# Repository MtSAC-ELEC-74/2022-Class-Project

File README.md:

# MtSAC ELEC 74 Spring Class Project
Please be aware that any contributions you make to this project are avaible to the public.

## KiCAD
Please use KiCAD V5.1.12 with this project.

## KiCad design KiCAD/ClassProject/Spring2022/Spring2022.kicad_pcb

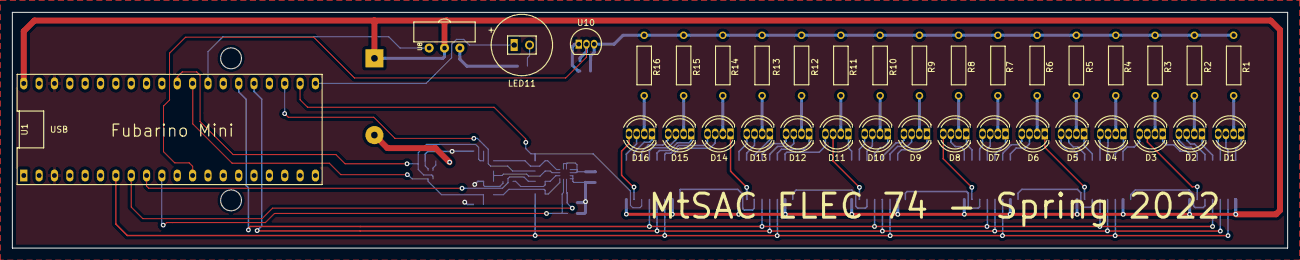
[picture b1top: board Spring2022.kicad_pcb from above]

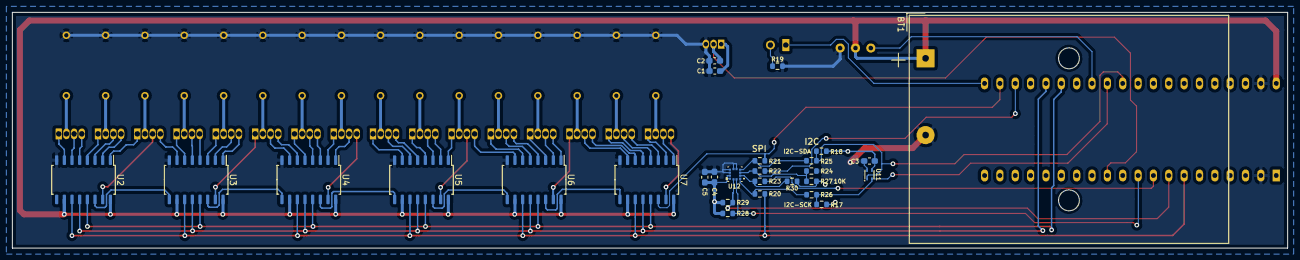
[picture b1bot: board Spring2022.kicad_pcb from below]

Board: 2 copper layers, 211.0 x 39.0 mm, 64 parts (28 on the bottom side), 90 nets.

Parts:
BT1: AAA-3x-Battery-Pack; BatteryHolder_Keystone_2479_3xAAA
C1, C2, C3, C4: PLP-000068; CAP-NON-POLAR-0603
C5: PLP-000409; CAP-NON-POLAR-0603
D1, D2, D3, D4, D5, D6, D7, D8, D9, D10, D11, D12, D13, D14, D15, D16: LED_RGBC; LED_D5.0mm-4_RGB
LED11: IRLED1503; IR1503
R1, R2, R3, R4, R5, R6, R7, R8, R9, R10, R11, R12, R13, R14, R15, R16: R; R-0.25W-THRU
R17, R18: PLP-000270; R_0603_1608Metric
R19: PLP-000031; R_0603_1608Metric
R20, R21, R22, R23, R24, R25, R26, R30: PLP-000091; R_0603_1608Metric
R27, R28, R29: PLP-000029; R_0603_1608Metric
U1: FUB-MINI; FubSocket_DIP-40_600_ELL
U2, U3, U4, U5, U6, U7: 74HC595; SOIC-16_4.55x10.3mm_P1.27mm
U8: PLP-000201
U10: LM35-LP; TO-92L_Inline
U11: SHT40-AD1B-R3; SHT4X
U12: LGA-12_STM; LIS2DE12TR

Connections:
+3V3: C1.1, C3.1, C4.1, C5.1, R17.1, R18.1, R27.1, R28.1, R29.1, R30.1, U1.3, U1.38, U10.1, U11.3, U12.9, U12.10
+4V: BT1.1, U1.40, U2.10, U2.16, U3.10, U3.16, U4.10, U4.16, U5.10, U5.16, U6.10, U6.16, U7.10, U7.16, U8.2
DISPLAY-CLK: U1.25, U2.12, U3.12, U4.12, U5.12, U6.12, U7.12
GND: BT1.2, C1.2, C2.2, C3.2, C4.2, C5.2, R1.1, R2.1, R3.1, R4.1, R5.1, R6.1, R7.1, R8.1, R9.1, R10.1, R11.1, R12.1, R13.1, R14.1, R15.1, R16.1, R19.2, R24.2, U1.2, U1.39, U2.8, U3.8, U4.8, U5.8, U6.8, U7.8, U8.1, U10.3, U11.4, U12.5, U12.6, U12.7, U12.8
I2C-SCK: R17.2, R26.1, U1.29, U11.2
I2C-SDA: R18.2, R25.1, U1.30, U11.1
IR-RX: U1.28, U8.3
IR-TX: LED11.1, U1.21
MISO: R22.1, U1.23
MOSI: R21.1, U1.22, U7.14
unnamed: D1.1, U2.7
unnamed: D1.2, R1.2
unnamed: D1.3, U2.6
unnamed: D1.4, U2.5
unnamed: D2.1, U2.4
unnamed: D2.2, R2.2
unnamed: D2.3, U2.3
unnamed: D2.4, U2.2
unnamed: D3.1, U2.1
unnamed: D3.2, R3.2
unnamed: D3.3, U2.15
unnamed: D3.4, U3.7
unnamed: D4.1, U3.6
unnamed: D4.2, R4.2
unnamed: D4.3, U3.5
unnamed: D4.4, U3.4
unnamed: D5.1, U3.3
unnamed: D5.2, R5.2
unnamed: D5.3, U3.2
unnamed: D5.4, U3.1
unnamed: D6.1, U3.15
unnamed: D6.2, R6.2
unnamed: D6.3, U4.7
unnamed: D6.4, U4.6
unnamed: D7.1, U4.5
unnamed: D7.2, R7.2
unnamed: D7.3, U4.4
unnamed: D7.4, U4.3
unnamed: D8.1, U4.2
unnamed: D8.2, R8.2
unnamed: D8.3, U4.1
unnamed: D8.4, U4.15
unnamed: D9.1, U5.7
unnamed: D9.2, R9.2
unnamed: D9.3, U5.6
unnamed: D9.4, U5.5
unnamed: D10.1, U5.4
unnamed: D10.2, R10.2
unnamed: D10.3, U5.3
unnamed: D10.4, U5.2
unnamed: D11.1, U5.1
unnamed: D11.2, R11.2
unnamed: D11.3, U5.15
unnamed: D11.4, U6.7
unnamed: D12.1, U6.6
unnamed: D12.2, R12.2
unnamed: D12.3, U6.5
unnamed: D12.4, U6.4
unnamed: D13.1, U6.3
unnamed: D13.2, R13.2
unnamed: D13.3, U6.2
unnamed: D13.4, U6.1
unnamed: D14.1, U6.15
unnamed: D14.2, R14.2
unnamed: D14.3, U7.7
unnamed: D14.4, U7.6
unnamed: D15.1, U7.5
unnamed: D15.2, R15.2
unnamed: D15.3, U7.4
unnamed: D15.4, U7.3
unnamed: D16.1, U7.2
unnamed: D16.2, R16.2
unnamed: D16.3, U7.1
unnamed: D16.4, U7.15
unnamed: LED11.2, R19.1
unnamed: R20.2, R26.2, U12.1
unnamed: R21.2, R25.2, U12.4
unnamed: R22.2, R24.1, R27.2, U12.3
unnamed: R23.2, R30.2, U12.2
unnamed: U2.14, U3.9
unnamed: U3.14, U4.9
unnamed: U4.14, U5.9
unnamed: U5.14, U6.9
unnamed: U6.14, U7.9
SCK: R20.1, U1.7, U2.11, U3.11, U4.11, U5.11, U6.11, U7.11
TEMPERATURE: C2.1, U1.12, U10.2
~CS-ACC: R23.1, U1.9
~INT1-ACC: R28.2, U1.10, U12.12
~INT2-ACC: R29.2, U1.8, U12.11
~LED-OE: U1.26, U2.13, U3.13, U4.13, U5.13, U6.13, U7.13

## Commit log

2022-03-19 Initial commit, added README.md
2022-03-19 Created KiCAD Project.
2022-03-25 Student Demo
2022-03-25 Test to schematic
2022-03-27 Added test project
    This is where I can put a longer description.
2022-03-27 Started working on the test program
    Wait for the serial port to open...
2022-03-28 Created IR Emitter Footprint
    I was working with two KiCAD pcb files so I deleted the one that was in my git folder and added the pcb file containing the IR footprint.
2022-04-01 Demo
2022-04-01 Library Folder and Patrick Library Folder
2022-04-01 Removed one KiCAD project file.
2022-04-01 Test again deleting sandbox 1
2022-04-01 Made R footprint
2022-04-01 Rain Gauge
2022-04-01 Added 555 Timer Footprint
2022-04-01 Removed extra folder
2022-04-01 Testing how to push
2022-04-01 to92
2022-04-01 Humidity Sensor Symbol
2022-04-01 Create Libraries and Patrick Library
2022-04-01 LED Footprint
    footprint for LED
2022-04-01 Move folder
2022-04-01 added to-92 footpring
2022-04-01 Added WiFi-LED sketch for ESP32-C3
2022-04-08 Added resistor to 74_jacob
2022-04-08 Added trace to R1
2022-04-08 Created library for IR Emitter
2022-04-08 Library moved to library folder
2022-04-08 ADDED mosfet SYMBOL
2022-04-08 added rescue lib
2022-04-08 Added new humidity temp sensor
2022-04-08 test
2022-04-08 Removed unused symbol
2022-04-08 ESP32-C3-MINI-1-N4 Symbol
2022-04-08 EPS32-C3-MINI-1 Footprint
2022-04-08 KiCad Cache file
2022-04-08 Added temp symbol
2022-04-08 ADDED footprint and Symbol for TO-92
2022-04-08 created IS1871SF bluetooth IC footprint and symbol
2022-04-08 Humidity Sensor
2022-04-08 Moved lib
2022-04-08 Added folder for lib
2022-04-08 Added symbol
2022-04-08 Humidity/Temp Sensor footprint
2022-04-08 Rain Gauge Symbol
2022-04-08 Matched Pins
2022-04-08 IR Footprint in library
2022-04-08 Matched Pins Schematic -> Footprint
2022-04-08 Moved Jay's project into a folder.
2022-04-08 removed aliases
2022-04-08 Added LIS2DE12TR Symbol, use LGA-12 for footprint
2022-04-15 Renamed and moved some libraries around.
2022-04-16 Renamed eduardo_arron
2022-04-16 Added more student footprints
2022-04-16 Added 74_ to all the footprint libraries.
2022-04-16 Added 555
2022-04-16 Moved 74_Kevin Lib
2022-04-16 Added ESP Wifi part
2022-04-16 Added 74_Kevin to schematic lib.
2022-04-16 Renamed Patrick lib
2022-04-16 Removed missing libraray
2022-04-16 Removed file causing errors.
2022-04-16 Deleted unneccesary folders
2022-04-16 Added ESP symbol to 74_Jacob lib
2022-04-16 Updated ESP symbol
2022-04-16 Connected footprint to symbol
2022-04-16 Made Patrick lib and moved ESP Symbol to Patrick lib
2022-04-17 Added 74595
2022-04-17 Footprint for FubSocket
2022-04-17 Added LED-Bar Schematic
2022-04-17 Added Fub Mini Sch Symbol and added to schematic.
2022-04-17 Wiring LED's
2022-04-17 Added Battery Holder
2022-04-17 Setup PCB and Annotated Parts
2022-04-22 Added relay footprint
2022-04-22 LED resistors update layout
2022-04-23 Added most other student parts.
2022-04-23 Add pontech KiCAD Library in the KiCAD project.
2022-04-23 Added decoupling caps and pull up resistors from PONTECH library
2022-04-23 Added accelerometer connections
2022-04-23 Added footprint for Mehdi's part.
2022-04-23 Wiring for accelerometer
2022-04-23 Added PLP-000029
2022-04-23 Added pull-up Resistors and Capacitors to accelerometer
2022-04-23 Added IR Tx
2022-04-23 Nearly finished schematic and routing.
2022-04-24 Updated humidity sensor
2022-04-24 Re-Saved humidity sensor changes to close KiCad
2022-04-29 Added Excel Spreadsheets for RGB Pattern Generation
2022-05-06 Sample project for reading accelerometer
2022-05-07 Schematic finished
2022-05-07 Added ESP32 but its going to come off before I am finished.
2022-05-07 Schematic Complete -> Need to finish routing
2022-05-07 PCB Layout Complete.
2022-05-11 Added board name to silkscreen.
2022-05-11 Checking and gerber generation.
2022-05-13 Added notes on excel formulas
2022-05-13 Added LCD project.
2022-05-13 Updated LCD Display
2022-05-20 RGB Spreadsheet
2022-05-27 Upgraded to KiCAD 6.0
2022-05-27 Auto stash before merge of "jacob" and "origin/jacob-home"
2022-05-27 Humidity sensor datasheet
2022-05-27 Working class project test code
2022-05-27 Renamed arduino folder to Arduino
2022-05-28 Revert "Upgraded to KiCAD 6.0"
    This reverts commit 6b4ca58081787079494b2a2522a3e7ee5416242f.
2022-05-28 led.display command working to display "MtSAC ELEC74 Spring 2022"
2022-05-28 Added function to display image based on accelerometer direction.
2022-05-28 Changed direction of accel direction.
2022-05-28 Added start up status color (green accelerometer good, red bad)
2022-05-28 Added level code, some weird one off errors are happening.
2022-06-03 Changes made while discussing project in class.
